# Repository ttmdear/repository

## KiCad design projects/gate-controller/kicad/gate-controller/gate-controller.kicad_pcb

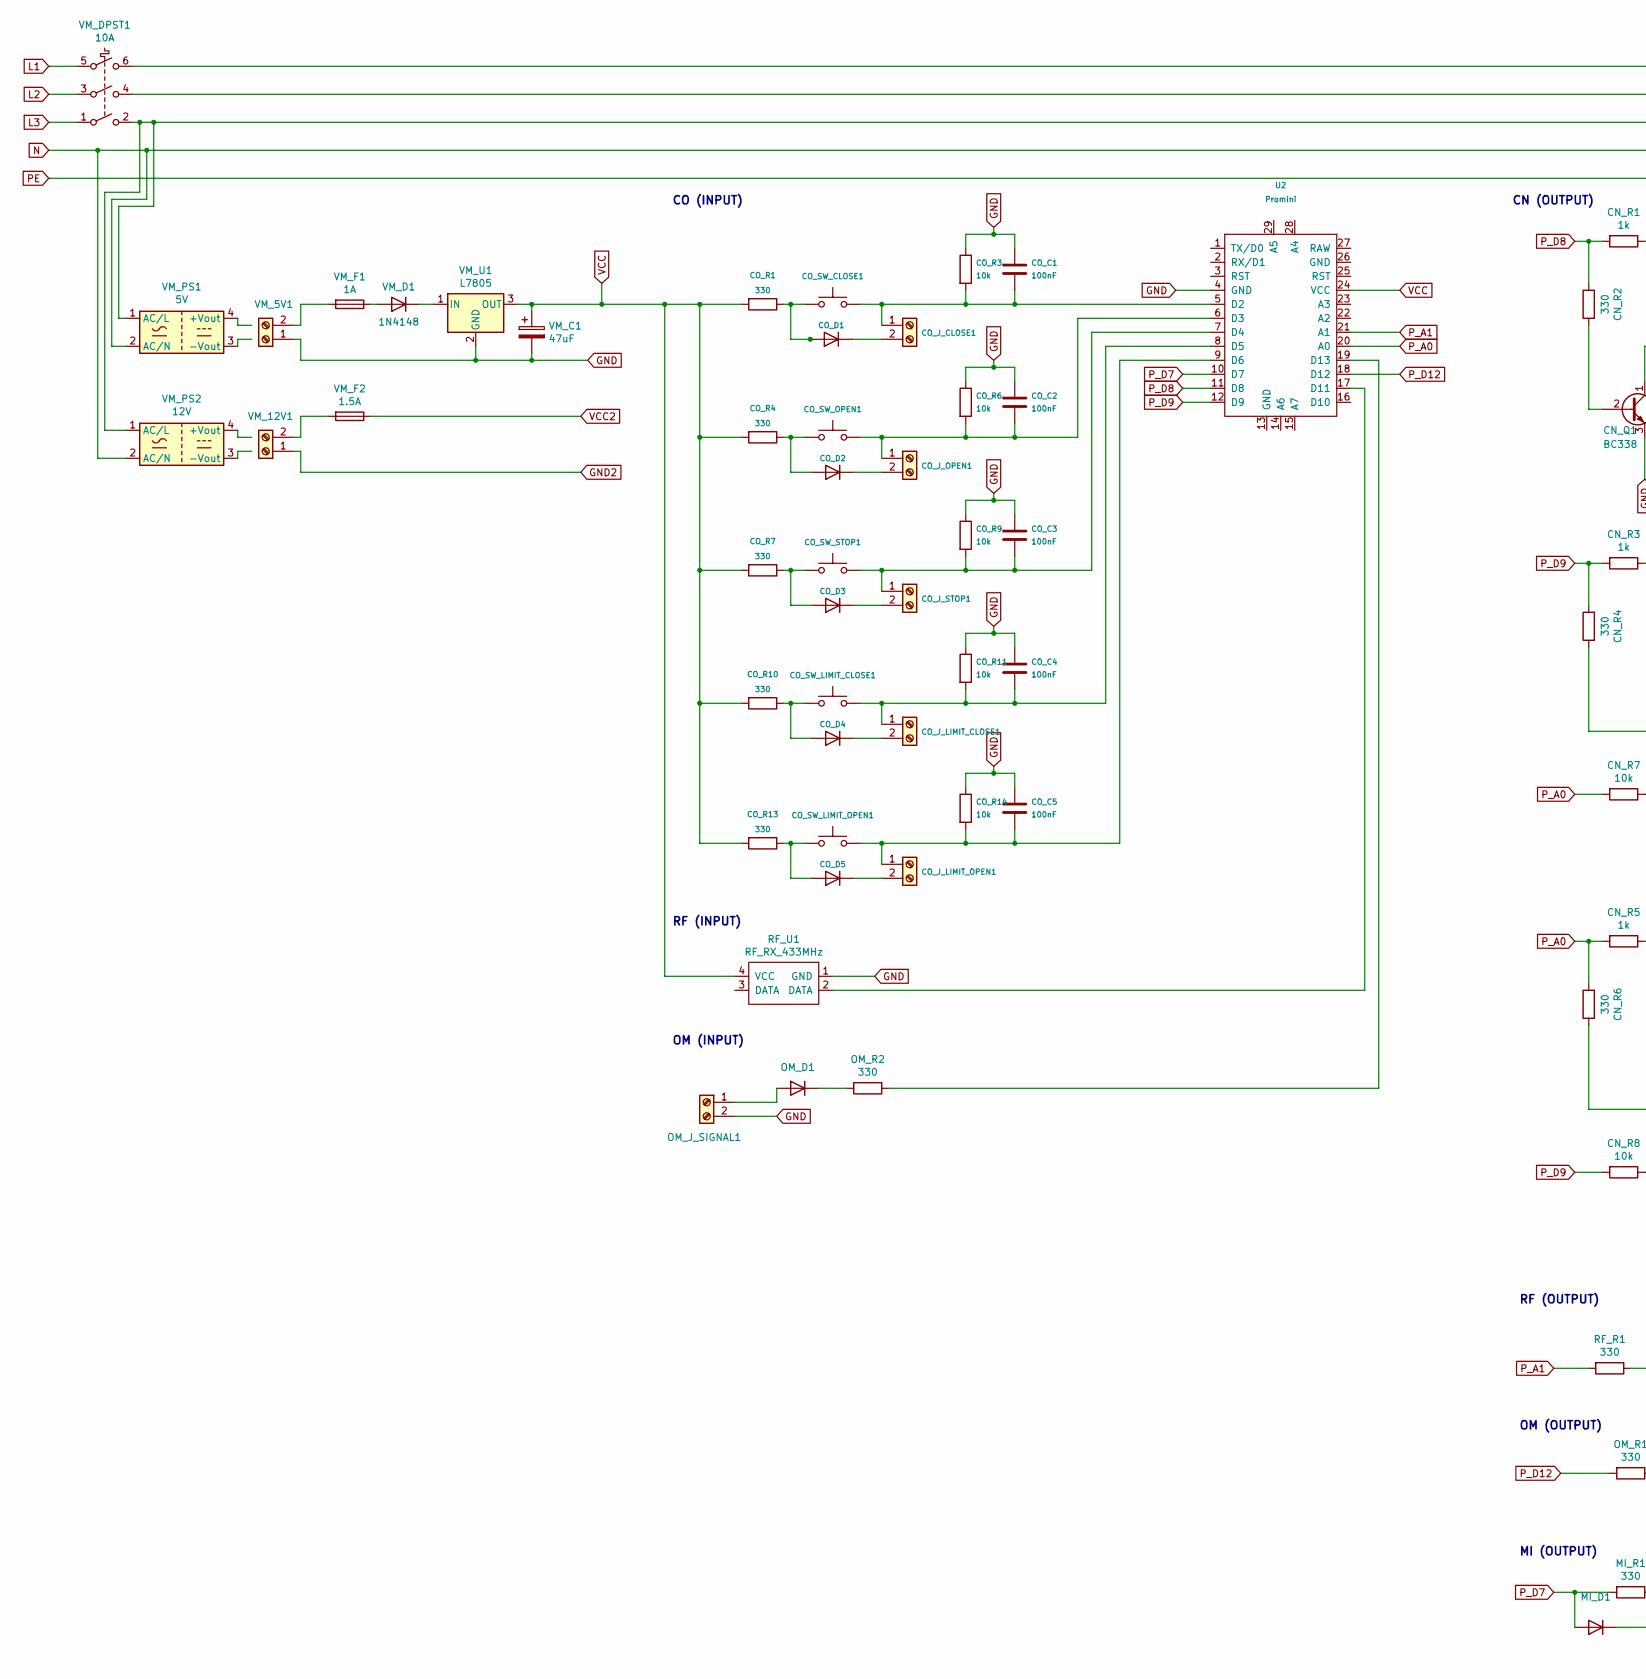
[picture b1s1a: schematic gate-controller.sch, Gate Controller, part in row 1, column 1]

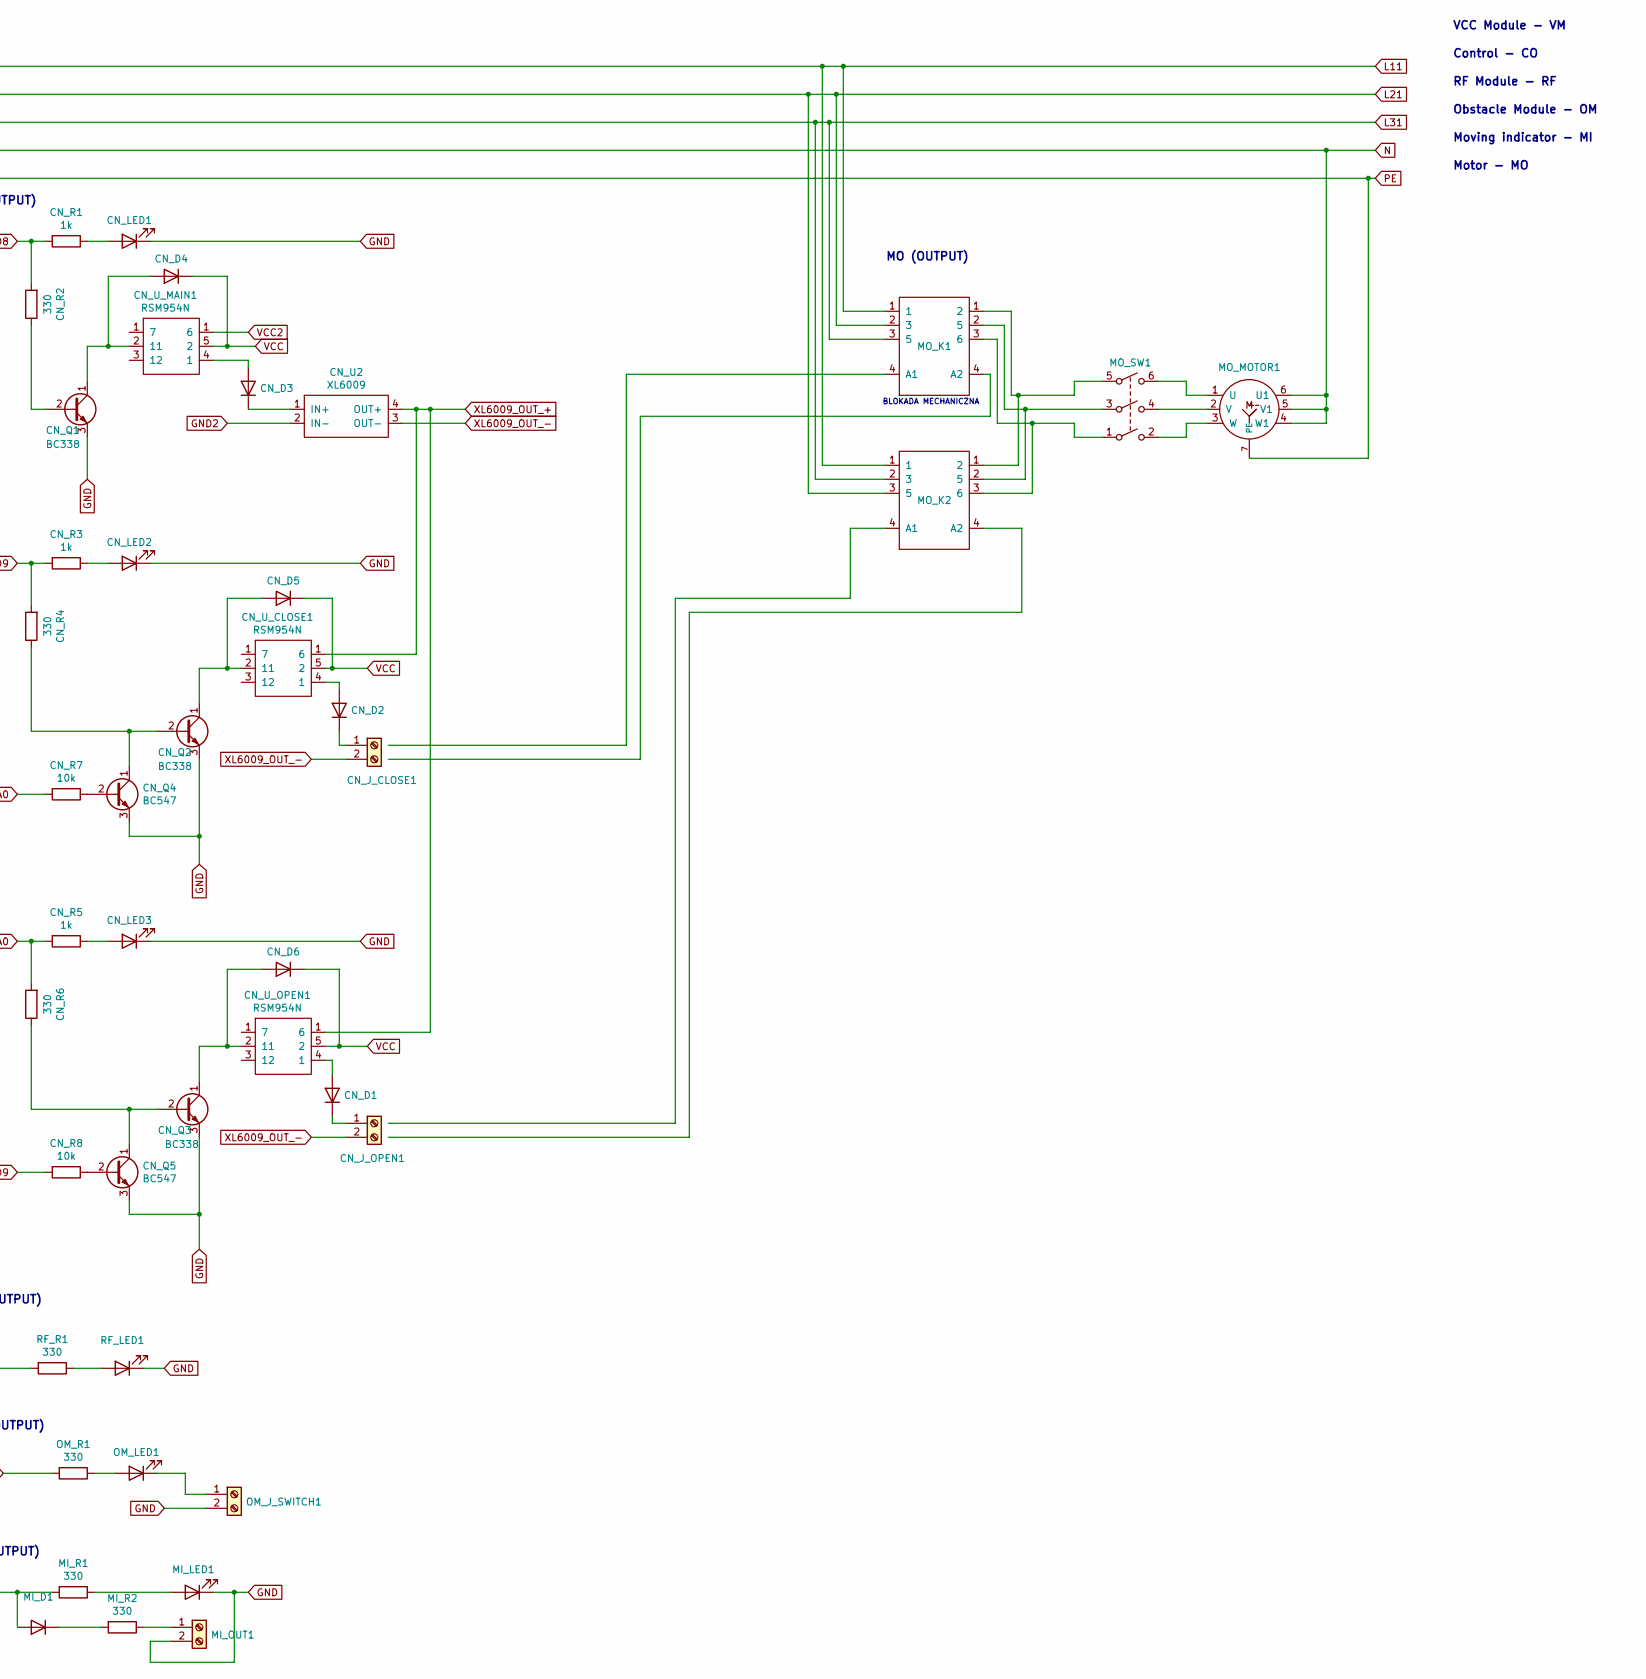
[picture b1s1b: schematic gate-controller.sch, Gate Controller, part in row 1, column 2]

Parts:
CN_D1, CN_D2, CN_D3, CN_D4, CN_D5, CN_D6: D; D_5W_P5.08mm_Vertical_AnodeUp
CN_J_CLOSE1: Screw_Terminal_01x02; TerminalBlock_bornier-2_P5.08mm
CN_J_OPEN1: Screw_Terminal_01x02; TerminalBlock_bornier-2_P5.08mm
CN_LED1, CN_LED2, CN_LED3: LED; D_5W_P5.08mm_Vertical_AnodeUp
CN_Q1, CN_Q2, CN_Q3: BC338; TO-92_Inline
CN_Q4, CN_Q5: BC547; TO-92_Inline
CN_R1, CN_R3, CN_R5: 1k; R_Axial_DIN0204_L3.6mm_D1.6mm_P5.08mm_Horizontal
CN_R2, CN_R4, CN_R6: 330; R_Axial_DIN0204_L3.6mm_D1.6mm_P5.08mm_Horizontal
CN_R7, CN_R8: 10k; R_Axial_DIN0204_L3.6mm_D1.6mm_P5.08mm_Horizontal
CN_U2: XL6009
CN_U_CLOSE1: RSM954N
CN_U_MAIN1: RSM954N
CN_U_OPEN1: RSM954N
CO_C1, CO_C2, CO_C3, CO_C4, CO_C5: 100nF; CP_Radial_D5.0mm_P2.50mm
CO_D1, CO_D2, CO_D3, CO_D4, CO_D5: D; D_5W_P5.08mm_Vertical_AnodeUp
CO_J_CLOSE1: Screw_Terminal_01x02; TerminalBlock_bornier-2_P5.08mm
CO_J_LIMIT_CLOSE1: Screw_Terminal_01x02; TerminalBlock_bornier-2_P5.08mm
CO_J_LIMIT_OPEN1: Screw_Terminal_01x02; TerminalBlock_bornier-2_P5.08mm
CO_J_OPEN1: Screw_Terminal_01x02; TerminalBlock_bornier-2_P5.08mm
CO_J_STOP1: Screw_Terminal_01x02; TerminalBlock_bornier-2_P5.08mm
CO_R1, CO_R4, CO_R7, CO_R10, CO_R13: 330; R_Axial_DIN0204_L3.6mm_D1.6mm_P5.08mm_Horizontal
CO_R3, CO_R6, CO_R9, CO_R11, CO_R14: 10k; R_Axial_DIN0204_L3.6mm_D1.6mm_P5.08mm_Horizontal
CO_SW_CLOSE1: SW_MEC_5G; SW_TH_Tactile_Omron_B3F-10xx
CO_SW_LIMIT_CLOSE1: SW_MEC_5G; SW_TH_Tactile_Omron_B3F-10xx
CO_SW_LIMIT_OPEN1: SW_MEC_5G; SW_TH_Tactile_Omron_B3F-10xx
CO_SW_OPEN1: SW_MEC_5G; SW_TH_Tactile_Omron_B3F-10xx
CO_SW_STOP1: SW_MEC_5G; SW_TH_Tactile_Omron_B3F-10xx
MI_D1: D; D_5W_P5.08mm_Vertical_AnodeUp
MI_LED1: LED; D_5W_P5.08mm_Vertical_AnodeUp
MI_OUT1: Screw_Terminal_01x02; TerminalBlock_bornier-2_P5.08mm
MI_R1, MI_R2: 330; R_Axial_DIN0204_L3.6mm_D1.6mm_P5.08mm_Horizontal
MO_K1, MO_K2: General_L3_K
MO_MOTOR1: 3_Phase_Star_Shaped_Motor
MO_SW1: MO_SW1
OM_D1: DIODE; D_5W_P5.08mm_Vertical_AnodeUp
OM_J_SIGNAL1: Screw_Terminal_01x02; TerminalBlock_bornier-2_P5.08mm
OM_J_SWITCH1: Screw_Terminal_01x02; TerminalBlock_bornier-2_P5.08mm
OM_LED1: LED; D_5W_P5.08mm_Vertical_AnodeUp
OM_R1, OM_R2: 330; R_Axial_DIN0204_L3.6mm_D1.6mm_P5.08mm_Horizontal
RF_LED1: LED; D_5W_P5.08mm_Vertical_AnodeUp
RF_R1: 330; R_Axial_DIN0204_L3.6mm_D1.6mm_P5.08mm_Horizontal
RF_U1: RF_RX_433MHz
U2: Promini; Arduino_Pro_Mini
VM_5V1, VM_12V1: Screw_Terminal_01x02; TerminalBlock_bornier-2_P5.08mm
VM_C1: 47uF; CP_Radial_D5.0mm_P2.50mm
VM_D1: 1N4148; D_5W_P5.08mm_Vertical_AnodeUp
VM_DPST1: 10A
VM_F1: 1A; Fuse_5X20
VM_F2: 1.5A; Fuse_5X20
VM_PS1: 5V; Converter_ACDC_HiLink_HLK-PMxx
VM_PS2: 12V; Converter_ACDC_HiLink_HLK-PMxx
VM_U1: L7805; TO-220-3_Vertical

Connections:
GND: CN_LED1.1 (K), CN_LED2.1 (K), CN_LED3.1 (K), CN_Q1.3 (E), CN_Q2.3 (E), CN_Q3.3 (E), CN_Q4.3 (E), CN_Q5.3 (E), CO_C1.1, CO_C2.1, CO_C3.1, CO_C4.1, CO_C5.1, CO_R3.1, CO_R6.1, CO_R9.1, CO_R11.1, CO_R14.1, MI_LED1.1 (K), MI_OUT1.2, OM_J_SIGNAL1.2, OM_J_SWITCH1.2, RF_LED1.1 (K), RF_U1.1 (GND), U2.4 (GND), VM_5V1.1, VM_C1.2, VM_U1.2 (GND)
GND2: CN_U2.2 (IN-), VM_12V1.1
unnamed: CN_D1.1 (K), CN_J_OPEN1.1
unnamed: CN_D1.2 (A), CN_U_OPEN1.4 (1)
unnamed: CN_D2.1 (K), CN_J_CLOSE1.1
unnamed: CN_D2.2 (A), CN_U_CLOSE1.4 (1)
unnamed: CN_D3.1 (K), CN_U2.1 (IN+)
unnamed: CN_D3.2 (A), CN_U_MAIN1.4 (1)
unnamed: CN_D4.2 (A), CN_Q1.1 (C), CN_U_MAIN1.2 (11)
unnamed: CN_D5.2 (A), CN_Q2.1 (C), CN_U_CLOSE1.2 (11)
unnamed: CN_D6.2 (A), CN_Q3.1 (C), CN_U_OPEN1.2 (11)
unnamed: CN_LED1.2 (A), CN_R1.1
unnamed: CN_LED2.2 (A), CN_R3.1
unnamed: CN_LED3.2 (A), CN_R5.1
unnamed: CN_Q1.2 (B), CN_R2.1
unnamed: CN_Q2.2 (B), CN_Q4.1 (C), CN_R4.1
unnamed: CN_Q3.2 (B), CN_Q5.1 (C), CN_R6.1
unnamed: CN_Q4.2 (B), CN_R7.1
unnamed: CN_Q5.2 (B), CN_R8.1
unnamed: CO_C1.2, CO_J_CLOSE1.1, CO_R3.2, CO_SW_CLOSE1.3 (B), CO_SW_CLOSE1.4 (B), U2.5 (D2)
unnamed: CO_C2.2, CO_J_OPEN1.1, CO_R6.2, CO_SW_OPEN1.3 (B), CO_SW_OPEN1.4 (B), U2.6 (D3)
unnamed: CO_C3.2, CO_J_STOP1.1, CO_R9.2, CO_SW_STOP1.3 (B), CO_SW_STOP1.4 (B), U2.7 (D4)
unnamed: CO_C4.2, CO_J_LIMIT_CLOSE1.1, CO_R11.2, CO_SW_LIMIT_CLOSE1.3 (B), CO_SW_LIMIT_CLOSE1.4 (B), U2.8 (D5)
unnamed: CO_C5.2, CO_J_LIMIT_OPEN1.1, CO_R14.2, CO_SW_LIMIT_OPEN1.3 (B), CO_SW_LIMIT_OPEN1.4 (B), U2.9 (D6)
unnamed: CO_D1.1 (K), CO_J_CLOSE1.2
unnamed: CO_D1.2 (A), CO_R1.1, CO_SW_CLOSE1.1 (A), CO_SW_CLOSE1.2 (A)
unnamed: CO_D2.1 (K), CO_J_OPEN1.2
unnamed: CO_D2.2 (A), CO_R4.1, CO_SW_OPEN1.1 (A), CO_SW_OPEN1.2 (A)
unnamed: CO_D3.1 (K), CO_J_STOP1.2
unnamed: CO_D3.2 (A), CO_R7.1, CO_SW_STOP1.1 (A), CO_SW_STOP1.2 (A)
unnamed: CO_D4.1 (K), CO_J_LIMIT_CLOSE1.2
unnamed: CO_D4.2 (A), CO_R10.1, CO_SW_LIMIT_CLOSE1.1 (A), CO_SW_LIMIT_CLOSE1.2 (A)
unnamed: CO_D5.1 (K), CO_J_LIMIT_OPEN1.2
unnamed: CO_D5.2 (A), CO_R13.1, CO_SW_LIMIT_OPEN1.1 (A), CO_SW_LIMIT_OPEN1.2 (A)
unnamed: MI_D1.1 (K), MI_R2.2
unnamed: MI_LED1.2 (A), MI_R1.1
unnamed: MI_OUT1.1, MI_R2.1
unnamed: MO_K1.1, MO_K2.1, MO_SW1.5, VM_DPST1.6
unnamed: MO_K1.2 (3), MO_K2.2 (3), MO_K2.3 (5), MO_SW1.3, VM_DPST1.4
unnamed: MO_K1.3 (5), MO_K2.2 (3), MO_K2.3 (5), MO_SW1.1, VM_DPST1.2, VM_PS1.1 (AC/L), VM_PS2.1 (AC/L)
unnamed: MO_MOTOR1.1 (U), MO_SW1.6
unnamed: MO_MOTOR1.2 (V), MO_SW1.4
unnamed: MO_MOTOR1.3 (W), MO_SW1.2
unnamed: MO_MOTOR1.4 (W1), MO_MOTOR1.5 (V1), MO_MOTOR1.6 (U1), VM_PS1.2 (AC/N), VM_PS2.2 (AC/N)
unnamed: OM_D1.1 (A), OM_J_SIGNAL1.1
unnamed: OM_D1.2 (K), OM_R2.1
unnamed: OM_J_SWITCH1.1, OM_LED1.1 (K)
unnamed: OM_LED1.2 (A), OM_R1.1
unnamed: OM_R2.2, U2.19 (D13)
unnamed: RF_LED1.2 (A), RF_R1.1
unnamed: RF_U1.2 (DATA), U2.17 (D11)
unnamed: VM_5V1.2, VM_F1.2
unnamed: VM_12V1.2, VM_F2.2
unnamed: VM_D1.1 (K), VM_U1.1 (IN)
unnamed: VM_D1.2 (A), VM_F1.1
P_A0: CN_R5.2, CN_R6.2, CN_R7.2, U2.20 (A0)
P_A1: RF_R1.2, U2.21 (A1)
P_D7: MI_D1.2 (A), MI_R1.2, U2.10 (D7)
P_D8: CN_R1.2, CN_R2.2, U2.11 (D8)
P_D9: CN_R3.2, CN_R4.2, CN_R8.2, U2.12 (D9)
P_D12: OM_R1.2, U2.18 (D12)
VCC: CN_D4.1 (K), CN_D5.1 (K), CN_D6.1 (K), CN_U_CLOSE1.5 (2), CN_U_MAIN1.5 (2), CN_U_OPEN1.5 (2), CO_R1.2, CO_R4.2, CO_R7.2, CO_R10.2, CO_R13.2, RF_U1.4 (VCC), U2.24 (VCC), VM_C1.1, VM_U1.3 (OUT)
VCC2: CN_U_MAIN1.1 (6), VM_F2.1
XL6009_OUT_+: CN_U2.4 (OUT+), CN_U_CLOSE1.1 (6), CN_U_OPEN1.1 (6)
XL6009_OUT_-: CN_J_CLOSE1.2, CN_J_OPEN1.2, CN_U2.3 (OUT-)

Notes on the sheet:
MI (OUTPUT)
OM (OUTPUT)
RF (INPUT)
MO (OUTPUT)
CO (INPUT)
VCC Module - VM
Control - CO
RF Module - RF
RF (OUTPUT)
Obstacle Module - OM
OM (INPUT)
Moving indicator - MI
CN (OUTPUT)
BLOKADA MECHANICZNA
Motor - MO

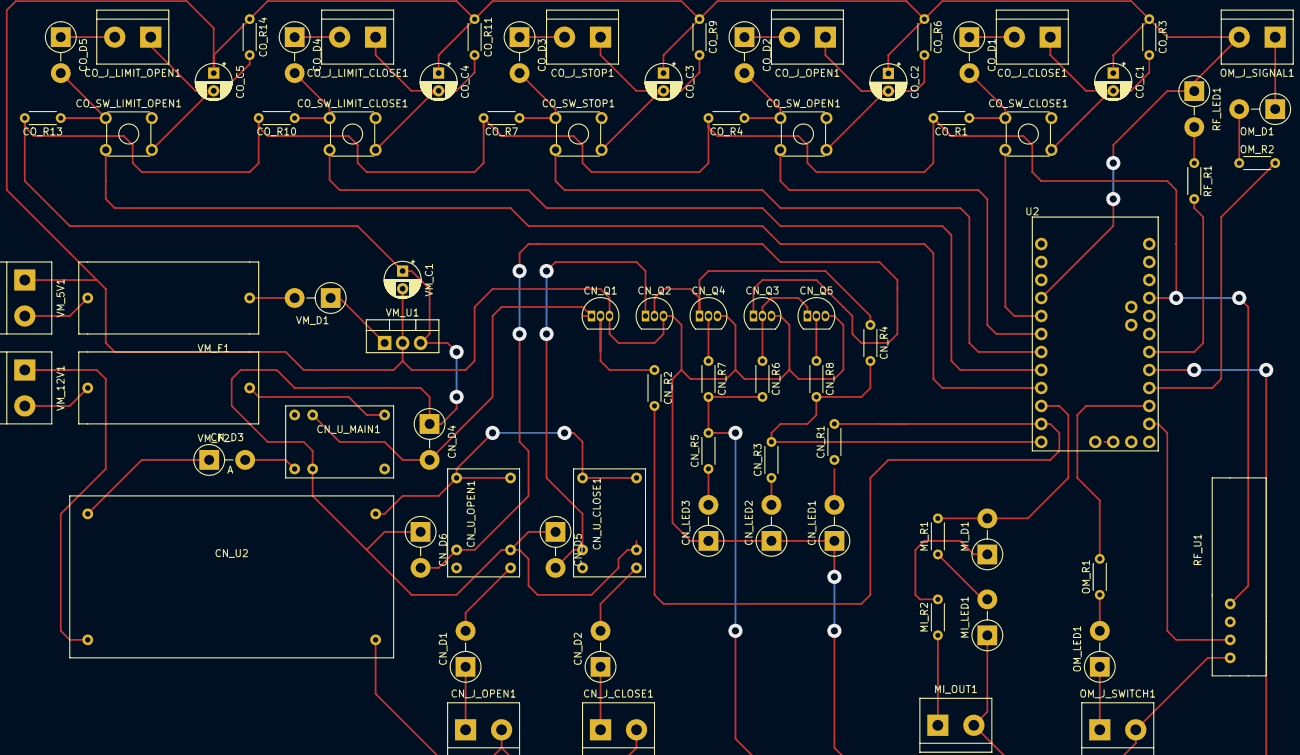
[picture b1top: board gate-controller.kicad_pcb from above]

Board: 2 copper layers, 80 parts (0 on the bottom side), 58 nets.

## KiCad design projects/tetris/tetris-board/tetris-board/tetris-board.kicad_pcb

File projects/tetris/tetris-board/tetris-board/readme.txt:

Wymiary: 110x200 mm
Liczba otworów: 196

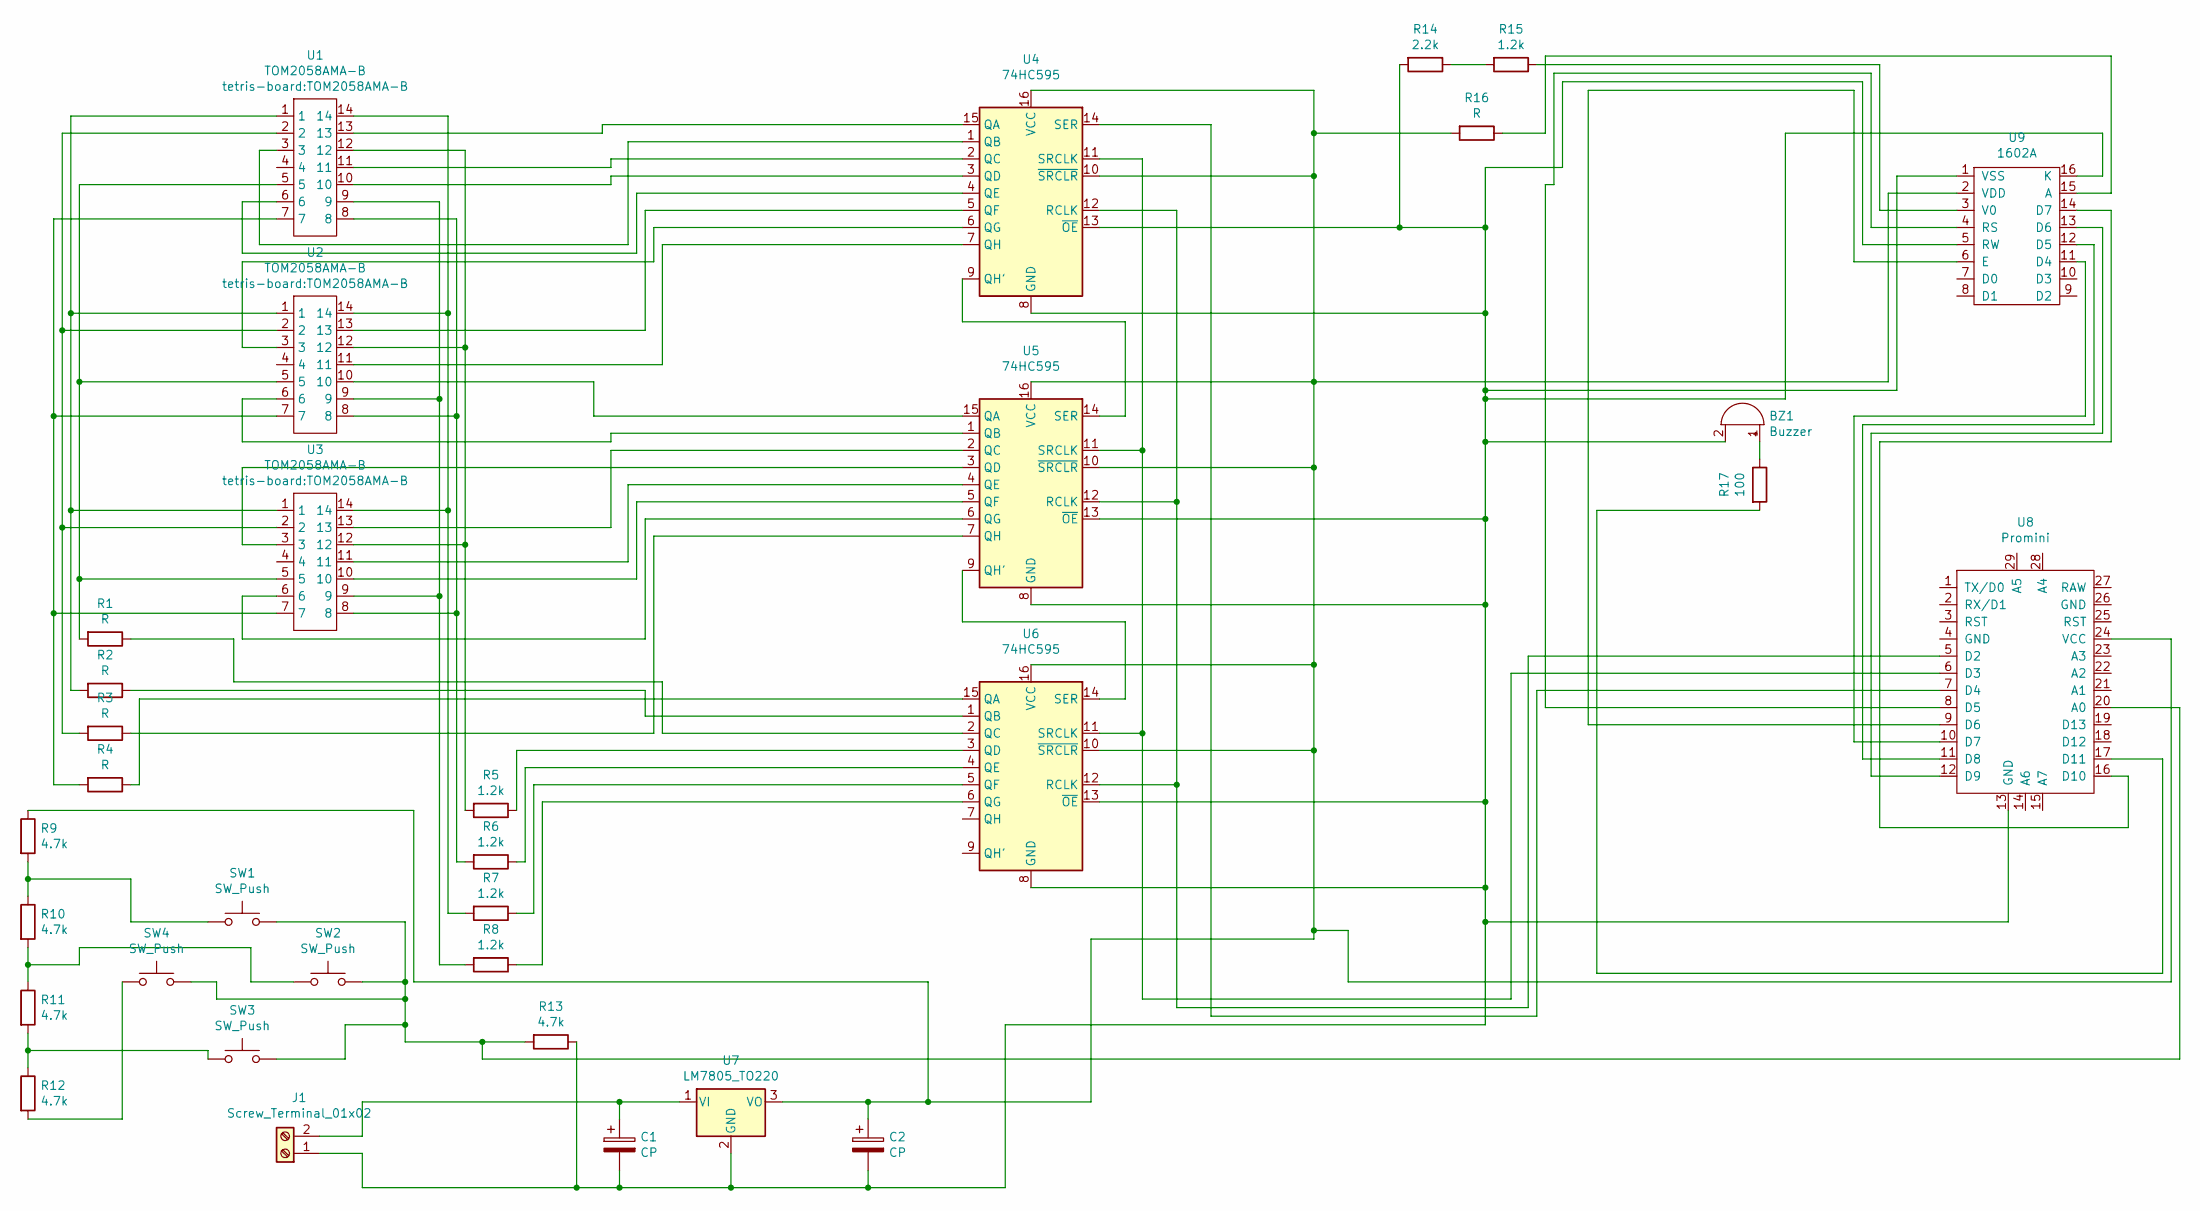
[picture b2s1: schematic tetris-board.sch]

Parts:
BZ1: Buzzer; Buzzer_12x9.5RM7.6
C1, C2: CP; CP_Radial_D5.0mm_P2.50mm
J1: Screw_Terminal_01x02; TerminalBlock_bornier-2_P5.08mm
R1, R2, R3, R4, R16: R; R_Axial_DIN0204_L3.6mm_D1.6mm_P5.08mm_Horizontal
R5, R6, R7, R8, R15: 1.2k; R_Axial_DIN0204_L3.6mm_D1.6mm_P5.08mm_Horizontal
R9, R10, R11, R12, R13: 4.7k; R_Axial_DIN0204_L3.6mm_D1.6mm_P5.08mm_Horizontal
R14: 2.2k; R_Axial_DIN0204_L3.6mm_D1.6mm_P5.08mm_Horizontal
R17: 100; R_Axial_DIN0204_L3.6mm_D1.6mm_P5.08mm_Horizontal
SW1, SW2, SW3, SW4: SW_Push; SW_PUSH_6mm
U1, U2, U3: TOM2058AMA-B
U4, U5, U6: 74HC595; DIP-16_W7.62mm
U7: LM7805_TO220; TO-220-3_Vertical
U8: Promini
U9: 1602A

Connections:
unnamed: BZ1.1 (-), R17.1
unnamed: BZ1.2 (+), C1.2, C2.2, J1.1, R13.1, R14.2, U4.8 (GND), U4.13 (~OE), U5.8 (GND), U5.13 (~OE), U6.8 (GND), U6.13 (~OE), U7.2 (GND), U8.13 (GND), U9.1 (VSS), U9.5 (RW), U9.16 (K)
unnamed: C1.1, J1.2, U7.1 (VI)
unnamed: C2.1, R9.1, R16.2, U4.10 (~SRCLR), U4.16 (VCC), U5.10 (~SRCLR), U5.16 (VCC), U6.10 (~SRCLR), U6.16 (VCC), U7.3 (VO), U8.24 (VCC), U9.2 (VDD)
unnamed: R1.1, U6.2 (QC)
unnamed: R1.2, U1.5, U2.5, U3.5
unnamed: R2.1, U6.1 (QB)
unnamed: R2.2, U1.1, U2.1, U3.1
unnamed: R3.1, U5.7 (QH)
unnamed: R3.2, U1.2, U2.2, U3.2
unnamed: R4.1, U6.15 (QA)
unnamed: R4.2, U1.7, U2.7, U3.7
unnamed: R5.1, U6.3 (QD)
unnamed: R5.2, U1.12, U2.12, U3.12
unnamed: R6.1, U6.4 (QE)
unnamed: R6.2, U1.8, U2.8, U3.8
unnamed: R7.1, U6.5 (QF)
unnamed: R7.2, U1.14, U2.14, U3.14
unnamed: R8.1, U6.6 (QG)
unnamed: R8.2, U1.9, U2.9, U3.9
unnamed: R9.2, R10.1, SW1.1
unnamed: R10.2, R11.1, SW2.1
unnamed: R11.2, R12.1, SW3.1
unnamed: R12.2, SW4.1
unnamed: R13.2, SW1.2, SW2.2, SW3.2, SW4.2, U8.20 (A0)
unnamed: R14.1, R15.2
unnamed: R15.1, U9.3 (V0)
unnamed: R16.1, U9.15 (A)
unnamed: R17.2, U8.17 (D11)
unnamed: U1.3, U4.1 (QB)
unnamed: U1.6, U4.4 (QE)
unnamed: U1.10, U4.3 (QD)
unnamed: U1.11, U4.2 (QC)
unnamed: U1.13, U4.15 (QA)
unnamed: U2.3, U4.6 (QG)
unnamed: U2.6, U5.1 (QB)
unnamed: U2.10, U5.15 (QA)
unnamed: U2.11, U4.7 (QH)
unnamed: U2.13, U4.5 (QF)
unnamed: U3.3, U5.3 (QD)
unnamed: U3.6, U5.6 (QG)
unnamed: U3.10, U5.5 (QF)
unnamed: U3.11, U5.4 (QE)
unnamed: U3.13, U5.2 (QC)
unnamed: U4.9 (QH'), U5.14 (SER)
unnamed: U4.11 (SRCLK), U5.11 (SRCLK), U6.11 (SRCLK), U8.6 (D3)
unnamed: U4.12 (RCLK), U5.12 (RCLK), U6.12 (RCLK), U8.5 (D2)
unnamed: U4.14 (SER), U8.7 (D4)
unnamed: U5.9 (QH'), U6.14 (SER)
unnamed: U8.8 (D5), U9.4 (RS)
unnamed: U8.9 (D6), U9.6 (E)
unnamed: U8.10 (D7), U9.11 (D4)
unnamed: U8.11 (D8), U9.12 (D5)
unnamed: U8.12 (D9), U9.13 (D6)
unnamed: U8.16 (D10), U9.14 (D7)

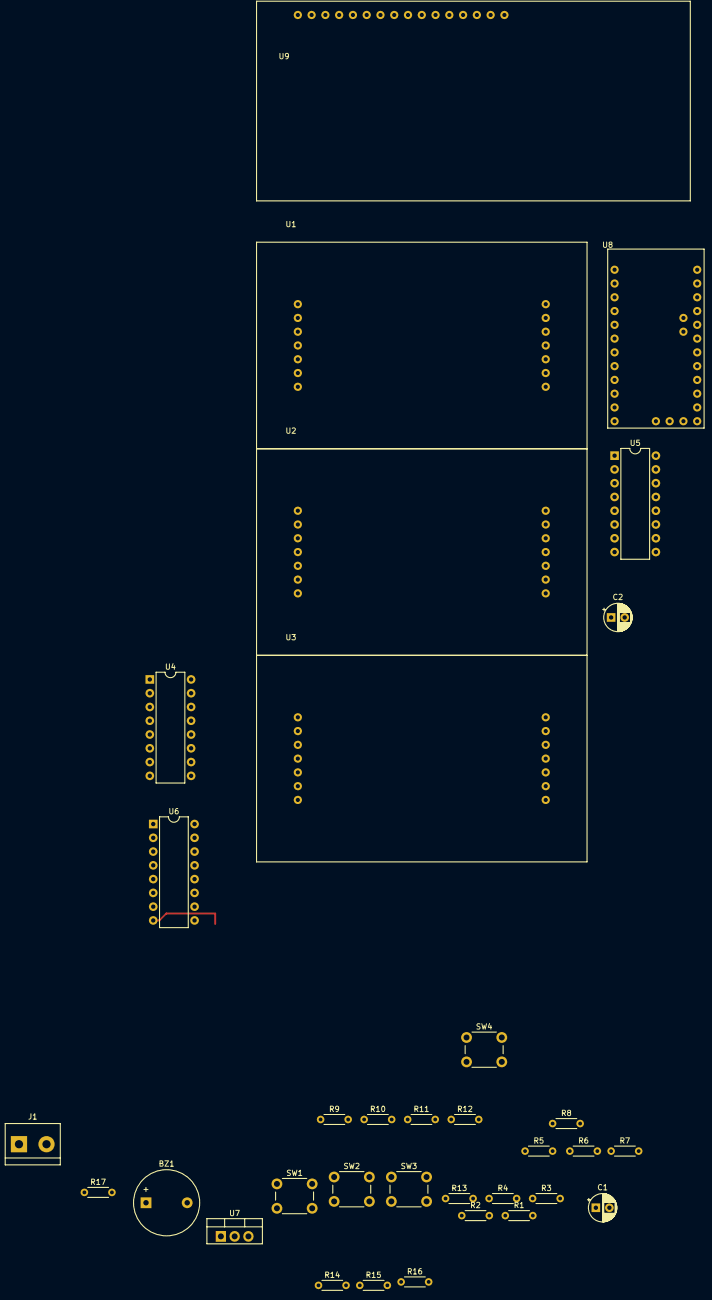
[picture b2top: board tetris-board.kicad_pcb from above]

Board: 2 copper layers, 34 parts (0 on the bottom side), 55 nets.

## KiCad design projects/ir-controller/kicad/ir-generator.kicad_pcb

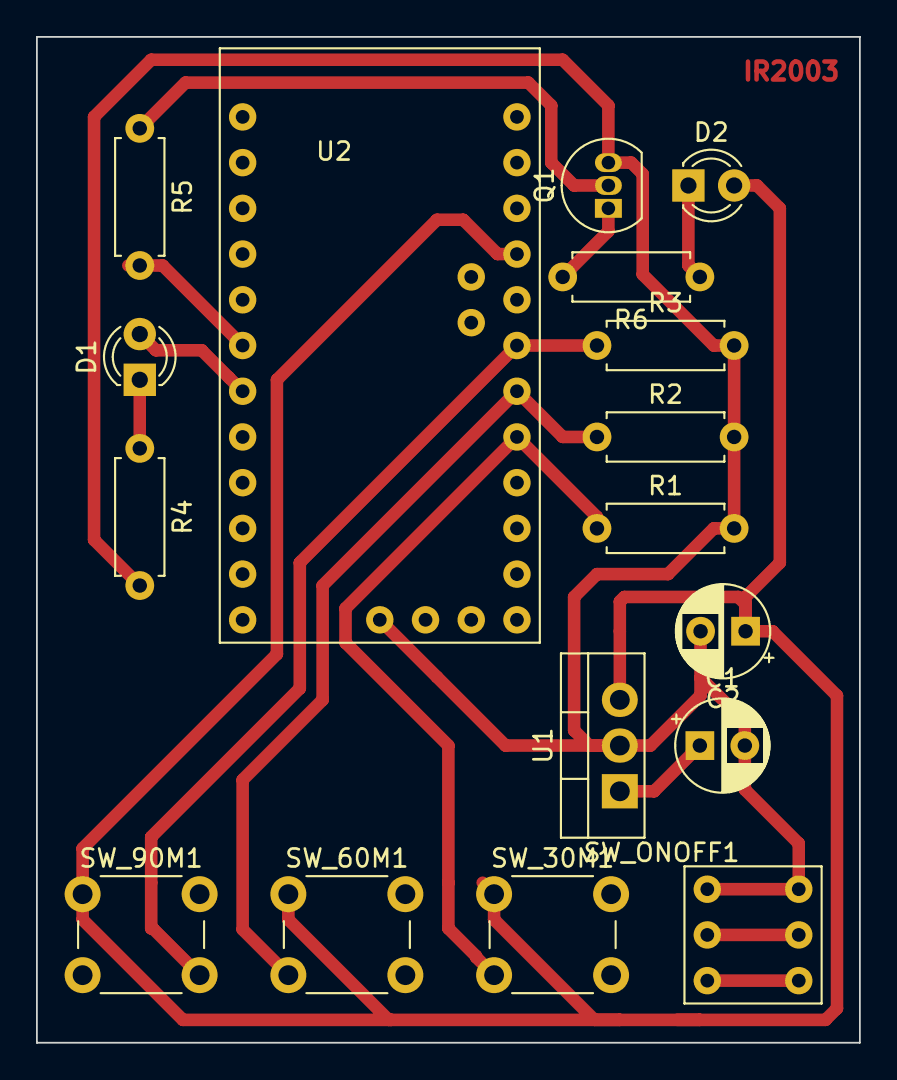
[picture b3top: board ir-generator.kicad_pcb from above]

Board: 2 copper layers, 45.7 x 55.9 mm, 17 parts (0 on the bottom side), 12 nets.

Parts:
C1: 0.33uF; CP_Radial_D5.0mm_P2.50mm
C2: 0.1uF; CP_Radial_D5.0mm_P2.50mm
D1, D2: LED; LED_D3.0mm
Q1: BC546; TO-92_Inline
R1, R2, R3, R5: 10k; R_Axial_DIN0207_L6.3mm_D2.5mm_P7.62mm_Horizontal
R4: 4.6k; R_Axial_DIN0207_L6.3mm_D2.5mm_P7.62mm_Horizontal
R6: 100; R_Axial_DIN0207_L6.3mm_D2.5mm_P7.62mm_Horizontal
SW_30M1, SW_60M1, SW_90M1: SW_DIP_x01; SW_PUSH_6mm
SW_ONOFF1: SW_DPDT_x2; Button_Switch_2x3_2.54mm
U1: LM7805_TO220; TO-220-3_Vertical
U2: Promini

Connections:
+9V: C1.1, U1.1
unnamed: C1.2, C2.2, Q1.3, R1.2, R2.2, R3.2, R4.2, SW_ONOFF1.1, U1.2, U2.13
unnamed: C2.1, D2.2, SW_30M1.1, SW_60M1.1, SW_90M1.1, U1.3, U2.24
unnamed: D1.1, R4.1
unnamed: D1.2, U2.7
unnamed: D2.1, R6.1
unnamed: Q1.1, R6.2
unnamed: Q1.2, R5.1
unnamed: R1.1, SW_30M1.2, U2.20
unnamed: R2.1, SW_60M1.2, U2.21
unnamed: R3.1, SW_90M1.2, U2.22
unnamed: R5.2, U2.6

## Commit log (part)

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2019-12-19 Init commit
2020-03-14 Developing
2020-08-04 images
2020-08-17 Increment
2020-09-03 Resource Bundles
2020-09-08 Remove target and idea files
2020-09-15 Change at Java tests
2020-09-15 Gate controller
2020-10-13 Bump junit from 3.8.1 to 4.13.1 in /kata/java-kata
    Bumps [junit](https://github.com/junit-team/junit4) from 3.8.1 to 4.13.1.
    - [Release notes](https://github.com/junit-team/junit4/releases)
    - [Changelog](https://github.com/junit-team/junit4/blob/main/doc/ReleaseNotes4.13.1.md)
    - [Commits](https://github.com/junit-team/junit4/commits/r4.13.1)
2020-10-13 Bump junit from 4.11 to 4.13.1 in /java/webservices
    Bumps [junit](https://github.com/junit-team/junit4) from 4.11 to 4.13.1.
    - [Release notes](https://github.com/junit-team/junit4/releases)
    - [Changelog](https://github.com/junit-team/junit4/blob/main/doc/ReleaseNotes4.11.md)
    - [Commits](https://github.com/junit-team/junit4/compare/r4.11...r4.13.1)
2020-10-13 Bump junit from 4.11 to 4.13.1 in /java/sercurity
    Bumps [junit](https://github.com/junit-team/junit4) from 4.11 to 4.13.1.
    - [Release notes](https://github.com/junit-team/junit4/releases)
    - [Changelog](https://github.com/junit-team/junit4/blob/main/doc/ReleaseNotes4.11.md)
    - [Commits](https://github.com/junit-team/junit4/compare/r4.11...r4.13.1)
2020-10-13 Bump junit from 4.11 to 4.13.1 in /java/logi
    Bumps [junit](https://github.com/junit-team/junit4) from 4.11 to 4.13.1.
    - [Release notes](https://github.com/junit-team/junit4/releases)
    - [Changelog](https://github.com/junit-team/junit4/blob/main/doc/ReleaseNotes4.11.md)
    - [Commits](https://github.com/junit-team/junit4/compare/r4.11...r4.13.1)
2020-10-13 Bump junit from 4.11 to 4.13.1 in /java/anotation-processing/app
    Bumps [junit](https://github.com/junit-team/junit4) from 4.11 to 4.13.1.
    - [Release notes](https://github.com/junit-team/junit4/releases)
    - [Changelog](https://github.com/junit-team/junit4/blob/main/doc/ReleaseNotes4.11.md)
    - [Commits](https://github.com/junit-team/junit4/compare/r4.11...r4.13.1)
2020-10-14 Bump junit from 4.11 to 4.13.1 in /java/com-repo-classloader
    Bumps [junit](https://github.com/junit-team/junit4) from 4.11 to 4.13.1.
    - [Release notes](https://github.com/junit-team/junit4/releases)
    - [Changelog](https://github.com/junit-team/junit4/blob/main/doc/ReleaseNotes4.11.md)
    - [Commits](https://github.com/junit-team/junit4/compare/r4.11...r4.13.1)
2020-11-04 [JAVA-SNIPPETS] Add some snippets.
2020-12-04 [JAVA-VALIDATION] Analysis of the JSR 303 specification
2020-12-04 [SPRING5-WEBFLUX] Some simple implementation of RestApi using reactive programming
2020-12-04 Różne zmiany.
2020-12-07 [SNIPPETS] Zainicjowanie prac.
2020-12-26 Pracę nad TETRIS V2
2020-12-27 Przeniesienie projektów do innego katalogu.
2021-01-06 [SNIPPETS] Check if resource exists.
2021-02-04 Increment.
2021-03-10 Bump junit from 4.11 to 4.13.1 in /java/java-validation
    Bumps [junit](https://github.com/junit-team/junit4) from 4.11 to 4.13.1.
    - [Release notes](https://github.com/junit-team/junit4/releases)
    - [Changelog](https://github.com/junit-team/junit4/blob/main/doc/ReleaseNotes4.11.md)
    - [Commits](https://github.com/junit-team/junit4/compare/r4.11...r4.13.1)
2021-03-10 Bump junit from 4.11 to 4.13.1 in /java/io
    Bumps [junit](https://github.com/junit-team/junit4) from 4.11 to 4.13.1.
    - [Release notes](https://github.com/junit-team/junit4/releases)
    - [Changelog](https://github.com/junit-team/junit4/blob/main/doc/ReleaseNotes4.11.md)
    - [Commits](https://github.com/junit-team/junit4/compare/r4.11...r4.13.1)
2021-03-10 Bump junit from 4.11 to 4.13.1 in /java/maven-exec
    Bumps [junit](https://github.com/junit-team/junit4) from 4.11 to 4.13.1.
    - [Release notes](https://github.com/junit-team/junit4/releases)
    - [Changelog](https://github.com/junit-team/junit4/blob/main/doc/ReleaseNotes4.11.md)
    - [Commits](https://github.com/junit-team/junit4/compare/r4.11...r4.13.1)
2021-03-10 Bump junit from 4.11 to 4.13.1 in /java/hibernate
    Bumps [junit](https://github.com/junit-team/junit4) from 4.11 to 4.13.1.
    - [Release notes](https://github.com/junit-team/junit4/releases)
    - [Changelog](https://github.com/junit-team/junit4/blob/main/doc/ReleaseNotes4.11.md)
    - [Commits](https://github.com/junit-team/junit4/compare/r4.11...r4.13.1)
2021-03-10 Bump junit from 4.11 to 4.13.1 in /java/patterns
    Bumps [junit](https://github.com/junit-team/junit4) from 4.11 to 4.13.1.
    - [Release notes](https://github.com/junit-team/junit4/releases)
    - [Changelog](https://github.com/junit-team/junit4/blob/main/doc/ReleaseNotes4.11.md)
    - [Commits](https://github.com/junit-team/junit4/compare/r4.11...r4.13.1)
2021-04-06 [JAVA] Junit4 @Rule.
2021-08-31 Bump junit from 4.11 to 4.13.1 in /java/java-serialization
    Bumps [junit](https://github.com/junit-team/junit4) from 4.11 to 4.13.1.
    - [Release notes](https://github.com/junit-team/junit4/releases)
    - [Changelog](https://github.com/junit-team/junit4/blob/main/doc/ReleaseNotes4.11.md)
    - [Commits](https://github.com/junit-team/junit4/compare/r4.11...r4.13.1)
    ---
    updated-dependencies:
2021-08-31 Bump junit from 4.11 to 4.13.1 in /java/java-annotations-processor
    Bumps [junit](https://github.com/junit-team/junit4) from 4.11 to 4.13.1.
    - [Release notes](https://github.com/junit-team/junit4/releases)
    - [Changelog](https://github.com/junit-team/junit4/blob/main/doc/ReleaseNotes4.11.md)
    - [Commits](https://github.com/junit-team/junit4/compare/r4.11...r4.13.1)
    ---
    updated-dependencies:
2021-08-31 Bump junit in /java/java-annotations-processor/processor
    Bumps [junit](https://github.com/junit-team/junit4) from 4.11 to 4.13.1.
    - [Release notes](https://github.com/junit-team/junit4/releases)
    - [Changelog](https://github.com/junit-team/junit4/blob/main/doc/ReleaseNotes4.11.md)
    - [Commits](https://github.com/junit-team/junit4/compare/r4.11...r4.13.1)
    ---
    updated-dependencies:
2021-08-31 Bump junit from 4.11 to 4.13.1 in /java/java-collections
    Bumps [junit](https://github.com/junit-team/junit4) from 4.11 to 4.13.1.
    - [Release notes](https://github.com/junit-team/junit4/releases)
    - [Changelog](https://github.com/junit-team/junit4/blob/main/doc/ReleaseNotes4.11.md)
    - [Commits](https://github.com/junit-team/junit4/compare/r4.11...r4.13.1)
    ---
    updated-dependencies:
2021-08-31 Bump junit from 4.11 to 4.13.1 in /java/java-reflection
    Bumps [junit](https://github.com/junit-team/junit4) from 4.11 to 4.13.1.
    - [Release notes](https://github.com/junit-team/junit4/releases)
    - [Changelog](https://github.com/junit-team/junit4/blob/main/doc/ReleaseNotes4.11.md)
    - [Commits](https://github.com/junit-team/junit4/compare/r4.11...r4.13.1)
    ---
    updated-dependencies:
2022-01-21 Bump h2 from 1.4.200 to 2.1.210 in /java/hibernate
    Bumps [h2](https://github.com/h2database/h2database) from 1.4.200 to 2.1.210.
    - [Release notes](https://github.com/h2database/h2database/releases)
    - [Commits](https://github.com/h2database/h2database/compare/version-1.4.200...version-2.1.210)
    ---
    updated-dependencies:
    - dependency-name: com.h2database:h2
2022-02-10 Bump hibernate-core from 5.4.11.Final to 5.4.24.Final in /java/hibernate
    Bumps [hibernate-core](https://github.com/hibernate/hibernate-orm) from 5.4.11.Final to 5.4.24.Final.
    - [Release notes](https://github.com/hibernate/hibernate-orm/releases)
    - [Changelog](https://github.com/hibernate/hibernate-orm/blob/5.4.24/changelog.txt)
    - [Commits](https://github.com/hibernate/hibernate-orm/compare/5.4.11...5.4.24)
    ---
    updated-dependencies:
2022-03-28 Bump junit from 4.11 to 4.13.1 in /java/junit4-rule
    Bumps [junit](https://github.com/junit-team/junit4) from 4.11 to 4.13.1.
    - [Release notes](https://github.com/junit-team/junit4/releases)
    - [Changelog](https://github.com/junit-team/junit4/blob/main/doc/ReleaseNotes4.11.md)
    - [Commits](https://github.com/junit-team/junit4/compare/r4.11...r4.13.1)
    ---
    updated-dependencies:
2022-03-28 Bump junit from 4.11 to 4.13.1 in /java/random
    Bumps [junit](https://github.com/junit-team/junit4) from 4.11 to 4.13.1.
    - [Release notes](https://github.com/junit-team/junit4/releases)
    - [Changelog](https://github.com/junit-team/junit4/blob/main/doc/ReleaseNotes4.11.md)
    - [Commits](https://github.com/junit-team/junit4/compare/r4.11...r4.13.1)
    ---
    updated-dependencies:
2022-03-28 Bump junit from 4.11 to 4.13.1 in /java/java-varhandle
    Bumps [junit](https://github.com/junit-team/junit4) from 4.11 to 4.13.1.
    - [Release notes](https://github.com/junit-team/junit4/releases)
    - [Changelog](https://github.com/junit-team/junit4/blob/main/doc/ReleaseNotes4.11.md)
    - [Commits](https://github.com/junit-team/junit4/compare/r4.11...r4.13.1)
    ---
    updated-dependencies:
2022-05-30 Bump junit from 4.11 to 4.13.1 in /java/reactor
    Bumps [junit](https://github.com/junit-team/junit4) from 4.11 to 4.13.1.
    - [Release notes](https://github.com/junit-team/junit4/releases)
    - [Changelog](https://github.com/junit-team/junit4/blob/main/doc/ReleaseNotes4.11.md)
    - [Commits](https://github.com/junit-team/junit4/compare/r4.11...r4.13.1)
    ---
    updated-dependencies:
2022-07-04 Bump jackson-databind from 2.7.4 to 2.12.6.1 in /java/poi-createword
    Bumps [jackson-databind](https://github.com/FasterXML/jackson) from 2.7.4 to 2.12.6.1.
    - [Release notes](https://github.com/FasterXML/jackson/releases)
    - [Commits](https://github.com/FasterXML/jackson/commits)
    ---
    updated-dependencies:
    - dependency-name: com.fasterxml.jackson.core:jackson-databind
2022-08-21 Bump junit from 4.11 to 4.13.1 in /java/java-string
    Bumps [junit](https://github.com/junit-team/junit4) from 4.11 to 4.13.1.
    - [Release notes](https://github.com/junit-team/junit4/releases)
    - [Changelog](https://github.com/junit-team/junit4/blob/main/doc/ReleaseNotes4.11.md)
    - [Commits](https://github.com/junit-team/junit4/compare/r4.11...r4.13.1)
    ---
    updated-dependencies:
2022-08-25 Bump junit from 4.11 to 4.13.1 in /java/java-basis
    Bumps [junit](https://github.com/junit-team/junit4) from 4.11 to 4.13.1.
    - [Release notes](https://github.com/junit-team/junit4/releases)
    - [Changelog](https://github.com/junit-team/junit4/blob/main/doc/ReleaseNotes4.11.md)
    - [Commits](https://github.com/junit-team/junit4/compare/r4.11...r4.13.1)
    ---
    updated-dependencies:
2022-10-25 Bump junit from 4.11 to 4.13.1 in /java/java-lang
    Bumps [junit](https://github.com/junit-team/junit4) from 4.11 to 4.13.1.
    - [Release notes](https://github.com/junit-team/junit4/releases)
    - [Changelog](https://github.com/junit-team/junit4/blob/main/doc/ReleaseNotes4.11.md)
    - [Commits](https://github.com/junit-team/junit4/compare/r4.11...r4.13.1)
    ---
    updated-dependencies:
2022-10-26 Bump junit from 4.11 to 4.13.1 in /java/cglib
    Bumps [junit](https://github.com/junit-team/junit4) from 4.11 to 4.13.1.
    - [Release notes](https://github.com/junit-team/junit4/releases)
    - [Changelog](https://github.com/junit-team/junit4/blob/main/doc/ReleaseNotes4.11.md)
    - [Commits](https://github.com/junit-team/junit4/compare/r4.11...r4.13.1)
    ---
    updated-dependencies:
2022-10-26 Bump junit from 4.11 to 4.13.1 in /java/java
    Bumps [junit](https://github.com/junit-team/junit4) from 4.11 to 4.13.1.
    - [Release notes](https://github.com/junit-team/junit4/releases)
    - [Changelog](https://github.com/junit-team/junit4/blob/main/doc/ReleaseNotes4.11.md)
    - [Commits](https://github.com/junit-team/junit4/compare/r4.11...r4.13.1)
    ---
    updated-dependencies:
2023-07-23 Bump org.springframework.boot:spring-boot-autoconfigure
    Bumps [org.springframework.boot:spring-boot-autoconfigure](https://github.com/spring-projects/spring-boot) from 2.2.3.RELEASE to 2.5.15.
    - [Release notes](https://github.com/spring-projects/spring-boot/releases)
    - [Commits](https://github.com/spring-projects/spring-boot/compare/v2.2.3.RELEASE...v2.5.15)
    ---
    updated-dependencies:
    - dependency-name: org.springframework.boot:spring-boot-autoconfigure
